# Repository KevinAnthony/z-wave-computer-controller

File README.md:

# z-wave-computer-controller
Code and diagrams to turn on and off a computer using z-wave.  Powered by a Z-UNO

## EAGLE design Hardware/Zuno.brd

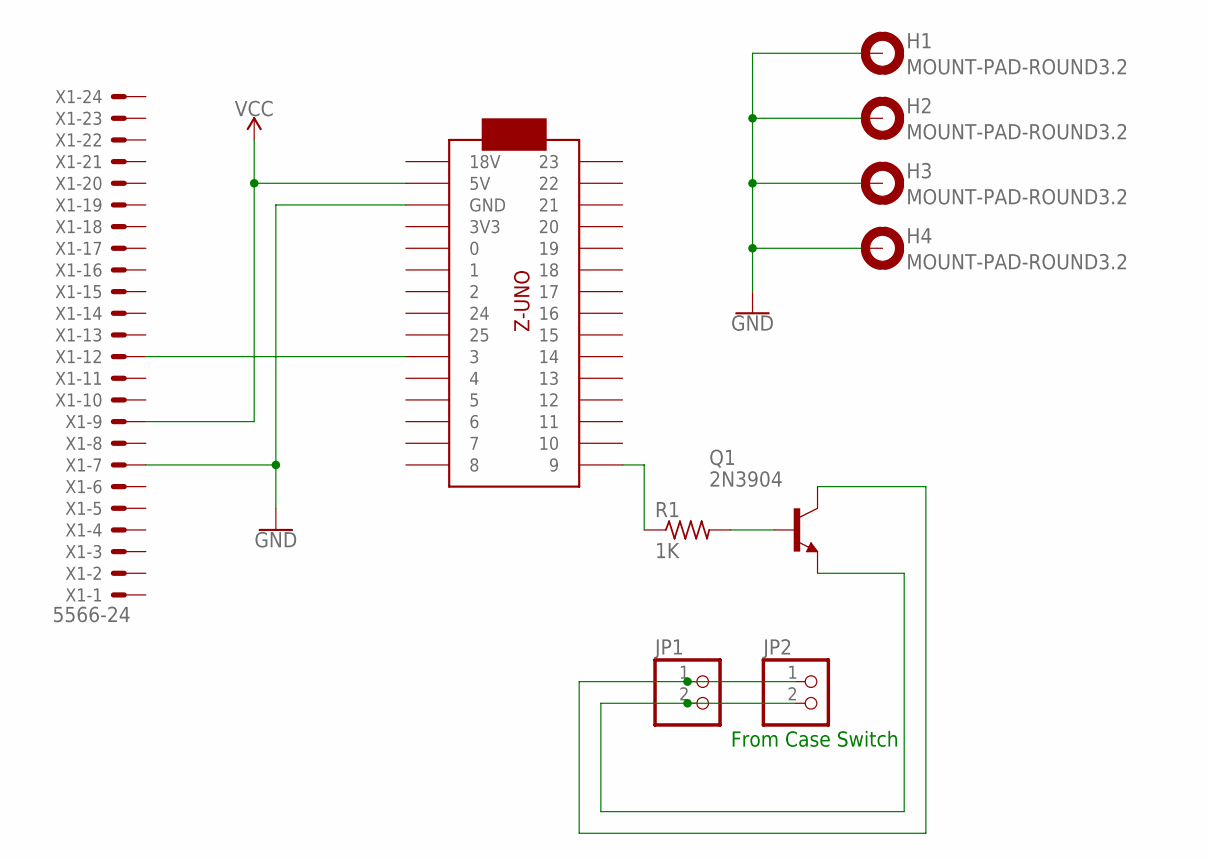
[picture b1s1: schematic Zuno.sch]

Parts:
H1, H2, H3, H4: MOUNT-PAD-ROUND3.2; 3,2-PAD
JP1, JP2: PINHD-1X2; 1X02
Q1: 2N3904; TO92
R1: 1K; 0207/10
U$1: ZUNO
X1: 5566-24

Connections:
GND: H1.B3,2, H2.B3,2, H3.B3,2, H4.B3,2, U$1.P$3 (GND), X1.7
unnamed: U$1.P$10 (3), X1.12
unnamed: R1.1, U$1.P$16 (9)
unnamed: Q1.2 (B), R1.2
unnamed: JP1.2, JP2.2, Q1.3 (E)
TOMOTHERBOARD: JP1.1, JP2.1, Q1.1 (C)
VCC: U$1.P$2 (5V), X1.9

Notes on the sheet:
From Case Switch

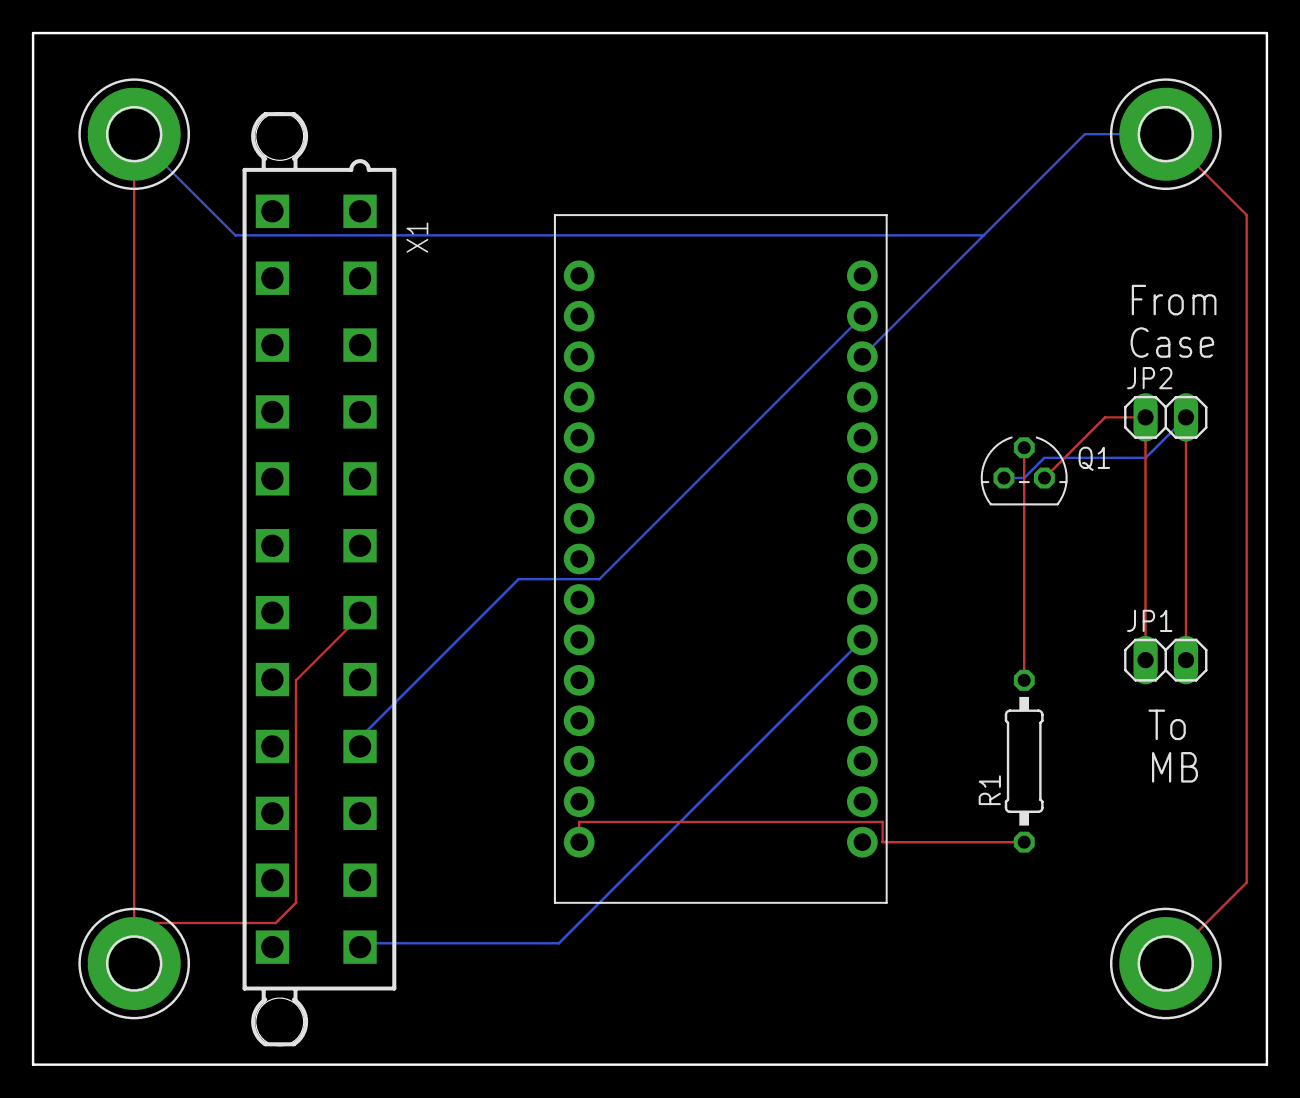
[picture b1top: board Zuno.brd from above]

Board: 2 copper layers, 77.5 x 64.8 mm, 10 parts (0 on the bottom side), 7 nets.

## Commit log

2017-07-27 Initial Commit of semi-working controller
2017-08-12 Updated board to include drill holes
2017-08-12 Added OSH Park Cam files

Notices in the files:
parts and their libraries:
SparkFun-PowerSymbols: Licensing: Creative Commons ShareAlike 4.0 International - https://creativecommons.org/licenses/by-sa/4.0
